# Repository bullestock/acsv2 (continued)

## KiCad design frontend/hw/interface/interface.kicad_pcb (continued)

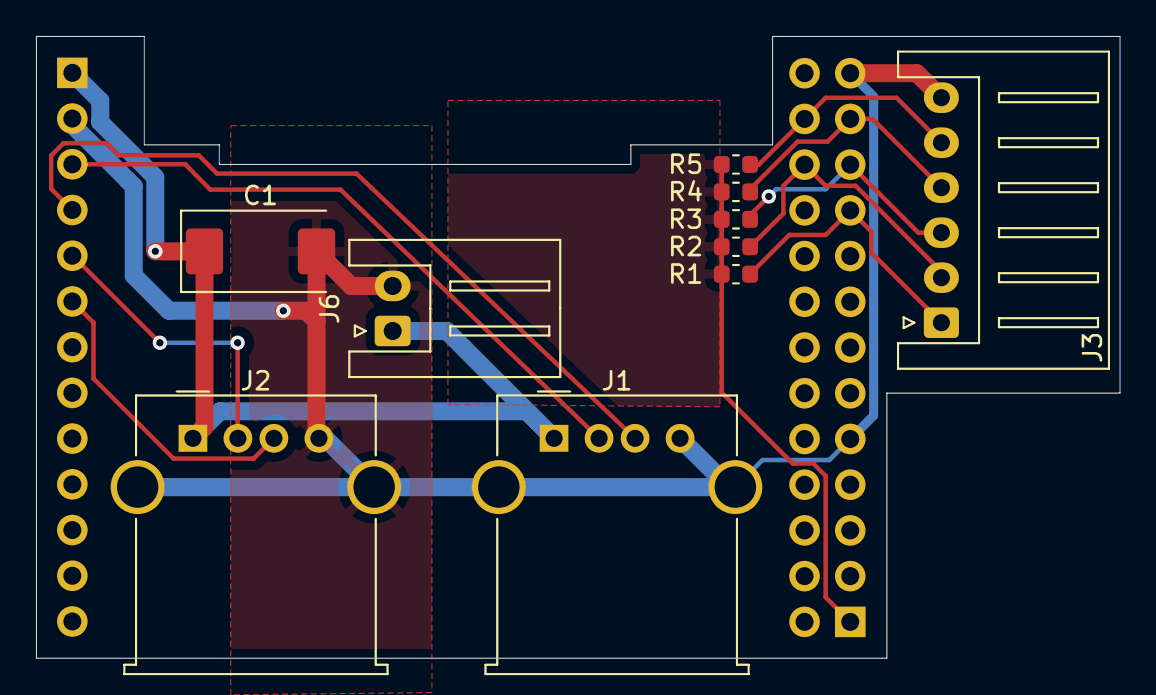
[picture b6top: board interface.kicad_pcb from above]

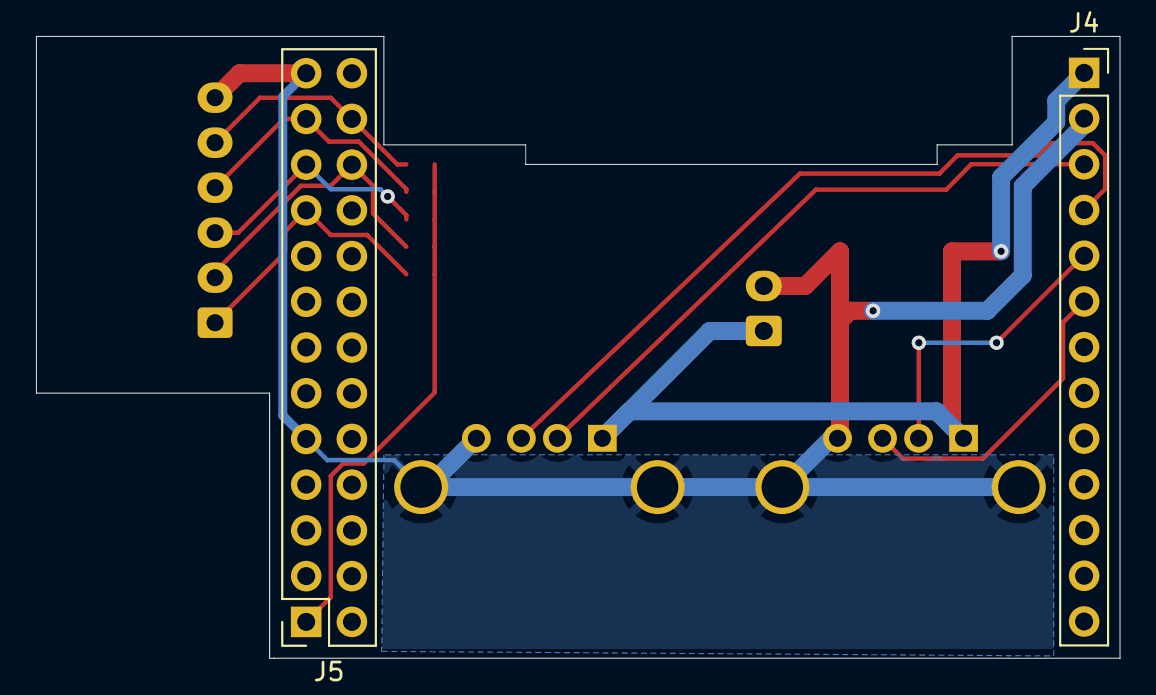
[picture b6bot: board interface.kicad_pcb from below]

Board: 2 copper layers, 60.2 x 34.5 mm, 12 parts (2 on the bottom side), 12 nets.

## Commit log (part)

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2023-09-18 Make slack.cpp compile.
2023-09-18 Fix backend logging.
2023-09-18 Only post status if it is set.
2023-09-18 Make Slack work.
2023-09-19 Start porting Card_cache; refactor.
2023-09-19 Port rest of Card_cache.
2023-09-20 Add missing slash, call to cleanup().
2023-09-20 Improve logging.
2023-09-22 Fix import.
2023-09-22 Make Card_cache work.
2023-09-22 Fix memory leak.
2023-09-22 Start porting Card_reader.
2023-09-22 Fix bugs.
2023-09-22 Reduce debug noise.
2023-09-23 Port Buttons.
2023-09-23 Refactor Display class.
2023-09-23 Port ForeningLet.
2023-09-23 Fix link errors.
2023-09-23 Configure button pins.
2023-09-23 Start cache task.
2023-09-23 Update card cache test.
2023-09-23 Fix debug.
2023-09-23 Fix stack overflow.
2023-09-23 Add line wrap.
2023-09-23 Start porting to CQ.
2023-09-23 Avoid that time moves around.
2023-09-23 Fix memory leak
2023-09-23 Add RAII wrapper for cJSON.
2023-09-24 Add ForeningLet setup.
2023-09-24 Fix format error.
2023-09-24 Add heap debug.
2023-09-24 Fix memory leaks
2023-09-24 Add uptime/mem output.
2023-09-24 Bump version
2023-09-25 Add support for devkit boards.
2023-09-25 Add foreninglet command
2023-09-25 Only update ForeningLet if card is valid.
2023-09-25 Add credentials check.
2023-09-25 Fix ForeningLet creds
2023-09-25 Fix concurrency problem.
2023-09-25 Force status update on start.
2023-09-25 Add status display
2023-09-25 Add line break.
2023-09-25 Show free memory in status line.
2023-09-25 Final CadQuery version.
2023-09-27 Clean up error logging
2023-09-27 Add bottom
2023-10-01 Update for ESP32 solution.
2023-10-03 Add RTS pullup; move RS485 connector.
2023-10-07 Add R10.
2023-10-12 Swap red/white, set production mode.
2023-10-12 Set UNLOCK_WARN to ten minutes.
2023-10-14 Enable logging to gateway.
2023-11-05 Show card ID in Slack message.
2023-11-06 Clean up logging.
2023-11-07 Add --preload to Gunicorn command to avoid multiple instances of scheduler.
2023-11-08 Integrate relay board components into main board. Add switches and LEDs.
2023-11-08 Make logging more compact.
2023-11-08 Add seconds display connector.
2023-11-08 Start placing additional components.
2023-11-08 Place remaining components.
2023-11-08 Add missing symbols and footprints.
2023-11-08 Complete routing.
2023-11-08 Fix last cosmetic issues.
2023-11-10 Remove extra space.
2023-11-20 Add smaller case.
2023-11-20 Update certificate.
2023-11-20 Update test card.
2023-11-20 Remove obsolete libs.
2023-11-20 Improve error logging.
2023-11-23 Reduce logging.
2023-12-02 Start updating for new pcb.
2023-12-02 Remove orphan silk screen.
2023-12-02 Only show countdown if remaining time is more than 10 seconds.
2023-12-02 Always pass card ID as integer.
2023-12-03 If we have no wifi creds, do not start threads that need a net connection.
2023-12-03 Add test_reader command.
2023-12-03 Avoid unlocking on boot.
2023-12-03 Wait for WiFi indefinitely.
2023-12-03 Make /acsaction work.
2023-12-05 Speed up unlocking.
2023-12-05 Allow avplug1 cutout to be easily enlarged.
2023-12-08 Optimize routing.
2023-12-22 Fix cover cutout.
2023-12-22 Make it possible to enter console if WiFi creds are wrong.
2023-12-26 Start adding support for uploading core dump after crash.
2023-12-26 Make Slack updates non-blocking.
2023-12-27 Add coredump console command.
2023-12-27 Add function to upload coredump (WIP).
2024-01-01 Reduce fillet radius to improve finish of bottom.
2024-01-01 Make both AV plugs same size.
2024-01-02 Adjust timeouts.
2024-01-07 Add list_wifi, ident commands. Use identifier when logging.
2024-01-07 Adjust display hole.
2024-01-11 Remove OPi version.
2024-01-11 Only show space open/closed message for main instance.
2024-01-11 Include ident in /acsstatus call.
2024-01-11 Use 'device' for consistency.
2024-01-13 Add ESP32 frontend KiCAD project in the correct place.
2024-01-13 Add reset/boot switches, minimize size.
2024-01-13 Make corners round.
2024-01-13 Fix outline.
2024-01-19 Adjust display opening.
2024-01-19 Reduce fill size.
2024-01-20 Add device ident to all Slack messages.
2024-01-20 Include device in payload for /acsquery.
2024-01-25 Add test_buttons command.
2024-01-25 Update root certificates.
2024-01-27 Use Hal9k footprint library.
2024-01-28 Only check Leave button in locked state.
2024-02-01 Read door input.
2024-02-01 Add missing identifier.
2024-02-03 Check allow_open in return value from /acsquery.
2024-02-06 Fix check for allow_open.
2024-02-06 Ensure that status updates soon after boot.
2024-02-06 Remove debug.
2024-02-09 Enlarge holes.
2024-02-16 Make clear_wifi work correctly.
2024-02-22 Log number of log buffer overflows.
2024-03-28 Show identifier on boot.
2024-03-28 Update for esp-idf 5.2.1.
2024-03-30 Do not use identifier until NVS has been read.
2024-03-30 Reduce image size.
2024-03-30 Add OTA partitions.
2024-03-31 Add card reader heartbeat timestamp to status.
2024-04-01 Use app version from image.
2024-04-01 Add initial OTA firmware update code.
2024-04-01 Finish OTA firmware update code.
2024-04-01 Show resistor references on silk screen.
2024-04-05 Allow setting definitions in environment.
2024-04-06 Avoid buffer overflow.
2024-04-07 Rename test_logger to logger_test; run stress test if argument supplied.
2024-04-07 Add error check.
2024-04-07 Remove track fragment
2024-04-07 Improve logging performance by reusing connection.
2024-04-13 Update for ESP-IDF 5.2.
2024-04-13 Show error LED pattern on loss of RS-485 communication.
2024-04-18 Fix scrolling bug.
2024-04-25 Disable coredump.
2024-04-25 Write to #jeg-står-herude-og-banker-på.
2024-04-29 Remove debug code.
2024-04-30 Enable core dump again.
2024-05-02 Add 1.3.11 firmware.
2024-05-04 Fix card reader heartbeat.
2024-05-26 Add support for beta program.
2024-05-26 Add button labels.
2024-06-06 Add 'reboot' action.
2024-06-09 Add descriptor NVS setting.
2024-06-09 Fix duplicate definition.
2024-06-09 Add missing variable.
2024-06-10 Add setdesc action.
2024-06-12 Fix reading of descriptor.
2024-06-13 Fix copy-paste error.
2024-06-13 Add Slack stress test.
2024-06-13 Set 'space open' status correctly.
2024-06-23 Include identifier in log "Access granted" message. Always use card cache.
2024-07-04 Add version to GW status. Show space as open for all instances.
2024-07-04 Save some space.
2024-07-04 Set version correctly.
2024-07-21 Add card ID to __str__() so that it is searchable.
2024-07-21 Revert "Add card ID to __str__() so that it is searchable."
    This reverts commit 38c62199dfb3e01649c9ce662df133e0f423af1a.
2024-07-21 Define search_fields.
2024-07-25 Add more files.
2024-07-25 Change display to SSD1306.
2024-07-25 Implement add_progress().
2024-08-05 Fix deprecation warnings.
2024-08-15 Fix hole sizes.
2024-08-23 Update box for new version.
2024-08-23 Fix HW init.
2024-08-24 Implement console commands.
2024-08-24 Fix bug in test_relay arg setup.
2024-08-24 Update pin assignments, reduce code size.
2024-08-25 Cover for HiLink input terminals.
2024-08-25 Update for new IEC plug.
2024-08-25 Move holes, fix power plug recess.
2024-08-25 Make Slack test work.
2024-08-26 Adjust HiLink, DSN sizes.
2024-08-26 Fix parsing of GW response.
2024-08-27 Implement OTA FWU.
2024-08-27 Implement handling of both relays.
2024-08-27 Remove Slack support.
2024-08-29 Hack display offset.
2024-08-29 Require multiple keypresses to enter console.
2024-08-30 Make relay state persistent.
2024-08-31 Add support for remote reboot.
2024-08-31 Show relay state on startup.
2024-08-31 Make clear() reset row.
2024-08-31 Include version info in heartbeat.
2024-09-05 Fix read of saved relay state.
2024-09-21 Holder for display.
2024-09-28 Print version on boot.
2024-09-29 Improve debug.
2024-09-29 Improve logging, update for ESP-IDF v5.3.
2024-09-29 Suppress WiFi warning messages.
2024-09-30 Add support for simulating unknown card swipe.
2024-10-01 Show uptime status page 75% of the time.
2024-10-01 Remove retry logic.
2024-10-05 Show door status on main display.
2024-10-05 Catch reuse of cards.
2024-10-05 Enable OTA update again.
2024-10-05 Add missing 'd' in uptime display.
2024-10-06 Set auth_plugin.
2024-10-06 Update to Python 3.11.
2024-10-06 Implement check for unique card ID.
2024-10-07 Set work dir.
2024-10-10 Only show 'Open' if any doors are open.
2024-10-10 Show space status
2024-10-10 Add debug.
2024-10-10 Fix compilation.
2024-10-10 Fix door status.
2024-10-17 Try to fix empty check.
2024-10-31 Fix open doors bug.
2024-12-28 Add v3/permissions.
2024-12-29 v3/permissions: Omit users with no card.
2025-02-08 1.4.7.
2025-02-08 Fix deprecation warning.
2025-02-09 Add experimental /v4/permissions endpoint.
2025-04-14 Suppress DEBUG messages from template system.
2025-04-14 Fix logger setting.
2025-07-13 Update to esp-idf 5.4.1.
2025-07-17 Update Django to v5.
2025-08-26 Disable HTTP debug.
2025-08-27 Add scheduled reboot every night.
2025-08-30 Make reboot time random.
2025-11-05 Bump django from 5.2.4 to 5.2.8 in /backend
    Bumps [django](https://github.com/django/django) from 5.2.4 to 5.2.8.
    - [Commits](https://github.com/django/django/compare/5.2.4...5.2.8)
    ---
    updated-dependencies:
    - dependency-name: django
    dependency-version: 5.2.8
2025-11-27 Add partition table.
2025-11-27 Add MQTT support.
2025-12-29 Add scheduled reboot.
2025-12-31 Log to GW.
2026-01-01 Start logger task.
2026-01-01 Add MQTT logger image.
2026-01-01 Set exec bit.
2026-01-01 Fix command.
2026-01-02 Fix port.
2026-01-03 Add SNTP, make logging work, make console work.
2026-01-03 Fix scheduled reboot.
2026-01-03 Add missing files.
2026-01-03 Fix arguments to esp_mqtt_client_enqueue().
2026-01-03 Fix URI.
2026-01-03 Remove coredump support, add MQTT logging.
2026-01-04 Disable OTA update if EXT1 is low.
2026-01-04 Disable coredump to flash.
2026-01-04 Use 3 AV connectors.
2026-01-04 Disable OTA check.
2026-01-05 Merge.
2026-01-05 Fix OTA.
2026-01-15 Fix topic name.
2026-01-15 Fix crash.
2026-01-15 Migrate logging to MQTT.
2026-01-15 Fix partitions, stack overflow etc.
2026-01-24 Publish space status to MQTT.
2026-02-03 Bump django from 5.2.9 to 5.2.11 in /backend
    Bumps [django](https://github.com/django/django) from 5.2.9 to 5.2.11.
    - [Commits](https://github.com/django/django/compare/5.2.9...5.2.11)
    ---
    updated-dependencies:
    - dependency-name: django
    dependency-version: 5.2.11
2026-03-04 Bump django from 5.2.11 to 5.2.12 in /backend
    Bumps [django](https://github.com/django/django) from 5.2.11 to 5.2.12.
    - [Commits](https://github.com/django/django/compare/5.2.11...5.2.12)
    ---
    updated-dependencies:
    - dependency-name: django
    dependency-version: 5.2.12
2026-03-26 Fix topic, add timestamps.
2026-03-26 Run apk as root.
2026-04-02 Add logrotate.
2026-04-02 Use dcron.
2026-04-03 Add wrapper.
2026-04-08 Bump django from 5.2.12 to 5.2.13 in /backend
    Bumps [django](https://github.com/django/django) from 5.2.12 to 5.2.13.
    - [Commits](https://github.com/django/django/compare/5.2.12...5.2.13)
    ---
    updated-dependencies:
    - dependency-name: django
    dependency-version: 5.2.13
2026-04-26 Do not run cron in foreground.
2026-05-08 Bump django from 5.2.13 to 5.2.14 in /backend
    Bumps [django](https://github.com/django/django) from 5.2.13 to 5.2.14.
    - [Commits](https://github.com/django/django/compare/5.2.13...5.2.14)
    ---
    updated-dependencies:
    - dependency-name: django
    dependency-version: 5.2.14
2026-05-20 Use Python.
2026-05-30 Sleep on errors.
2026-06-02 Enable cross-signed certs.
2026-06-04 Add MQTT timestamp.
2026-06-04 Make MQTT payload pure JSON.
2026-06-05 Reduce number of connection attempts.
2026-06-06 Migrate status to MQTT.
2026-06-06 Subscribe to MQTT.
2026-06-06 Refactor MQTT.
2026-06-06 Migrate 'open doors' to MQTT.
2026-06-07 Update status display.
2026-06-07 Gateway: Use static allocation.
2026-06-07 Clan up debug prints.
2026-06-07 Use hourly log rotation.
2026-06-13 Use bar as separator.
2026-06-14 Distinguish log lines in 'docker logs' output.
2026-06-14 Omit topic stem.
2026-06-15 Adjust DEFAULT_BACKUP_COUNT.
2026-06-25 Fix rollover.
2026-06-26 Log backend logging errors to MQTT.
2026-06-27 Change wording.
